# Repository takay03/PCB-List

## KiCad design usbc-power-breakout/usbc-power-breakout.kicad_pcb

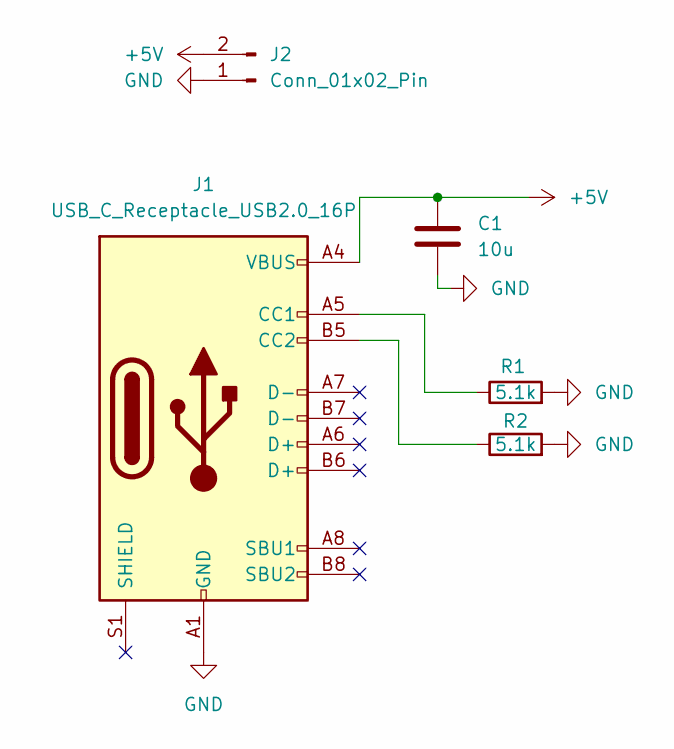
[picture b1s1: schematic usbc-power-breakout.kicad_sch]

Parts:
C1: 10u; C_1206_3216Metric
J1: USB_C_Receptacle_USB2.0_16P; USB_C_Receptacle_GCT_USB4085
J2: Conn_01x02_Pin; PinHeader_1x02_P2.54mm_Vertical
R1, R2: 5.1k; R_1206_3216Metric

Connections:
+5V: C1.1, J1.A4 (VBUS), J1.A9 (VBUS), J1.B4 (VBUS), J1.B9 (VBUS), J2.2
GND: C1.2, J1.A1 (GND), J1.A12 (GND), J1.B1 (GND), J1.B12 (GND), J2.1, R1.2, R2.2
unnamed: J1.A5 (CC1), R1.1
unnamed: J1.B5 (CC2), R2.1

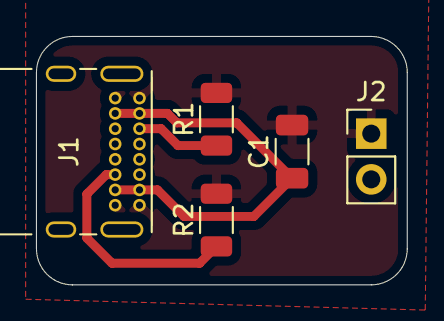
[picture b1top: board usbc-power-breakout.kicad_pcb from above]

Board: 2 copper layers, 20.6 x 13.8 mm, 5 parts (0 on the bottom side), 4 nets.

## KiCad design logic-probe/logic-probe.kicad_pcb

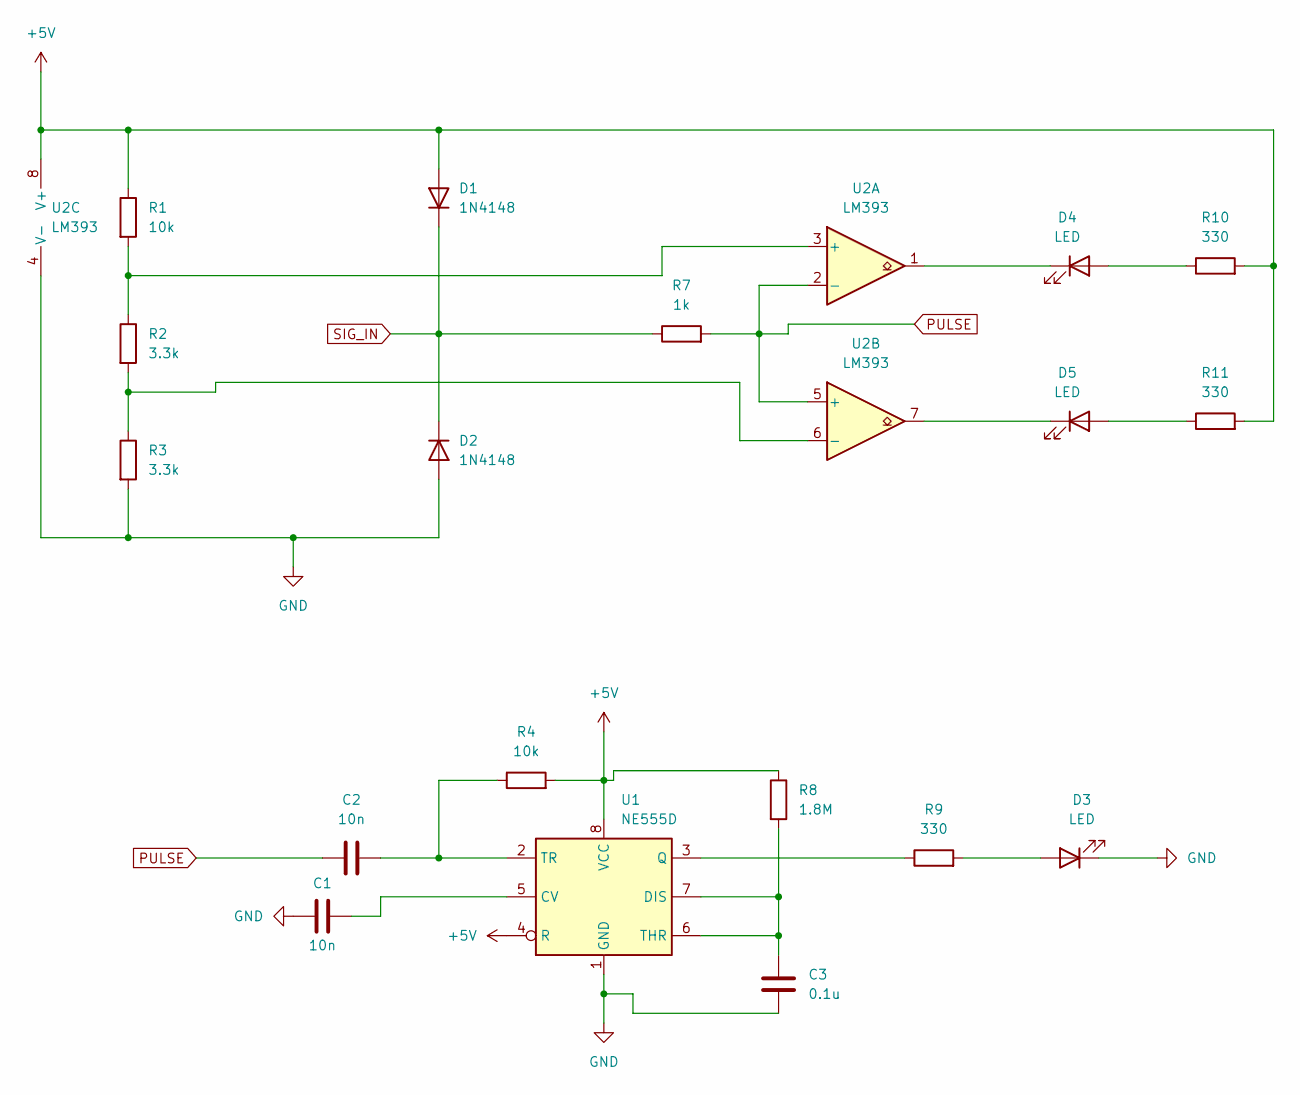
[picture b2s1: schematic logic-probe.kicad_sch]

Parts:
C1, C2: 10n; C_1206_3216Metric
C3: 0.1u; C_1206_3216Metric
D1, D2: 1N4148; D_SOD-123
D3, D4, D5: LED; LED_1206_3216Metric
R1, R4: 10k; R_1206_3216Metric
R2, R3: 3.3k; R_1206_3216Metric
R7: 1k; R_1206_3216Metric
R8: 1.8M; R_0805_2012Metric
R9, R10, R11: 330; R_1206_3216Metric
U1: NE555D; SOIC-8_3.9x4.9mm_P1.27mm
U2: LM393; SOIC-8_3.9x4.9mm_P1.27mm

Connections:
+5V: D1.2 (A), R1.1, R4.2, R8.1, R10.2, R11.2, U1.4 (R), U1.8 (VCC), U2.8 (V+)
GND: C1.1, C3.1, D2.2 (A), D3.1 (K), R3.2, U1.1 (GND), U2.4 (V-)
unnamed: D3.2 (A), R9.2
unnamed: D4.2 (A), R10.1
unnamed: D4.1 (K), U2.1
unnamed: D5.2 (A), R11.1
unnamed: D5.1 (K), U2.7
unnamed: C1.2, U1.5 (CV)
unnamed: C3.2, R8.2, U1.6 (THR), U1.7 (DIS)
unnamed: R9.1, U1.3 (Q)
unnamed: C2.2, R4.1, U1.2 (TR)
unnamed: R1.2, R2.1, U2.3 (+)
unnamed: R2.2, R3.1, U2.6 (-)
PULSE: C2.1, R7.2, U2.2 (-), U2.5 (+)
SIG_IN: D1.1 (K), D2.1 (K), R7.1

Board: 2 copper layers, 19 parts (0 on the bottom side), 15 nets, no tracks yet.

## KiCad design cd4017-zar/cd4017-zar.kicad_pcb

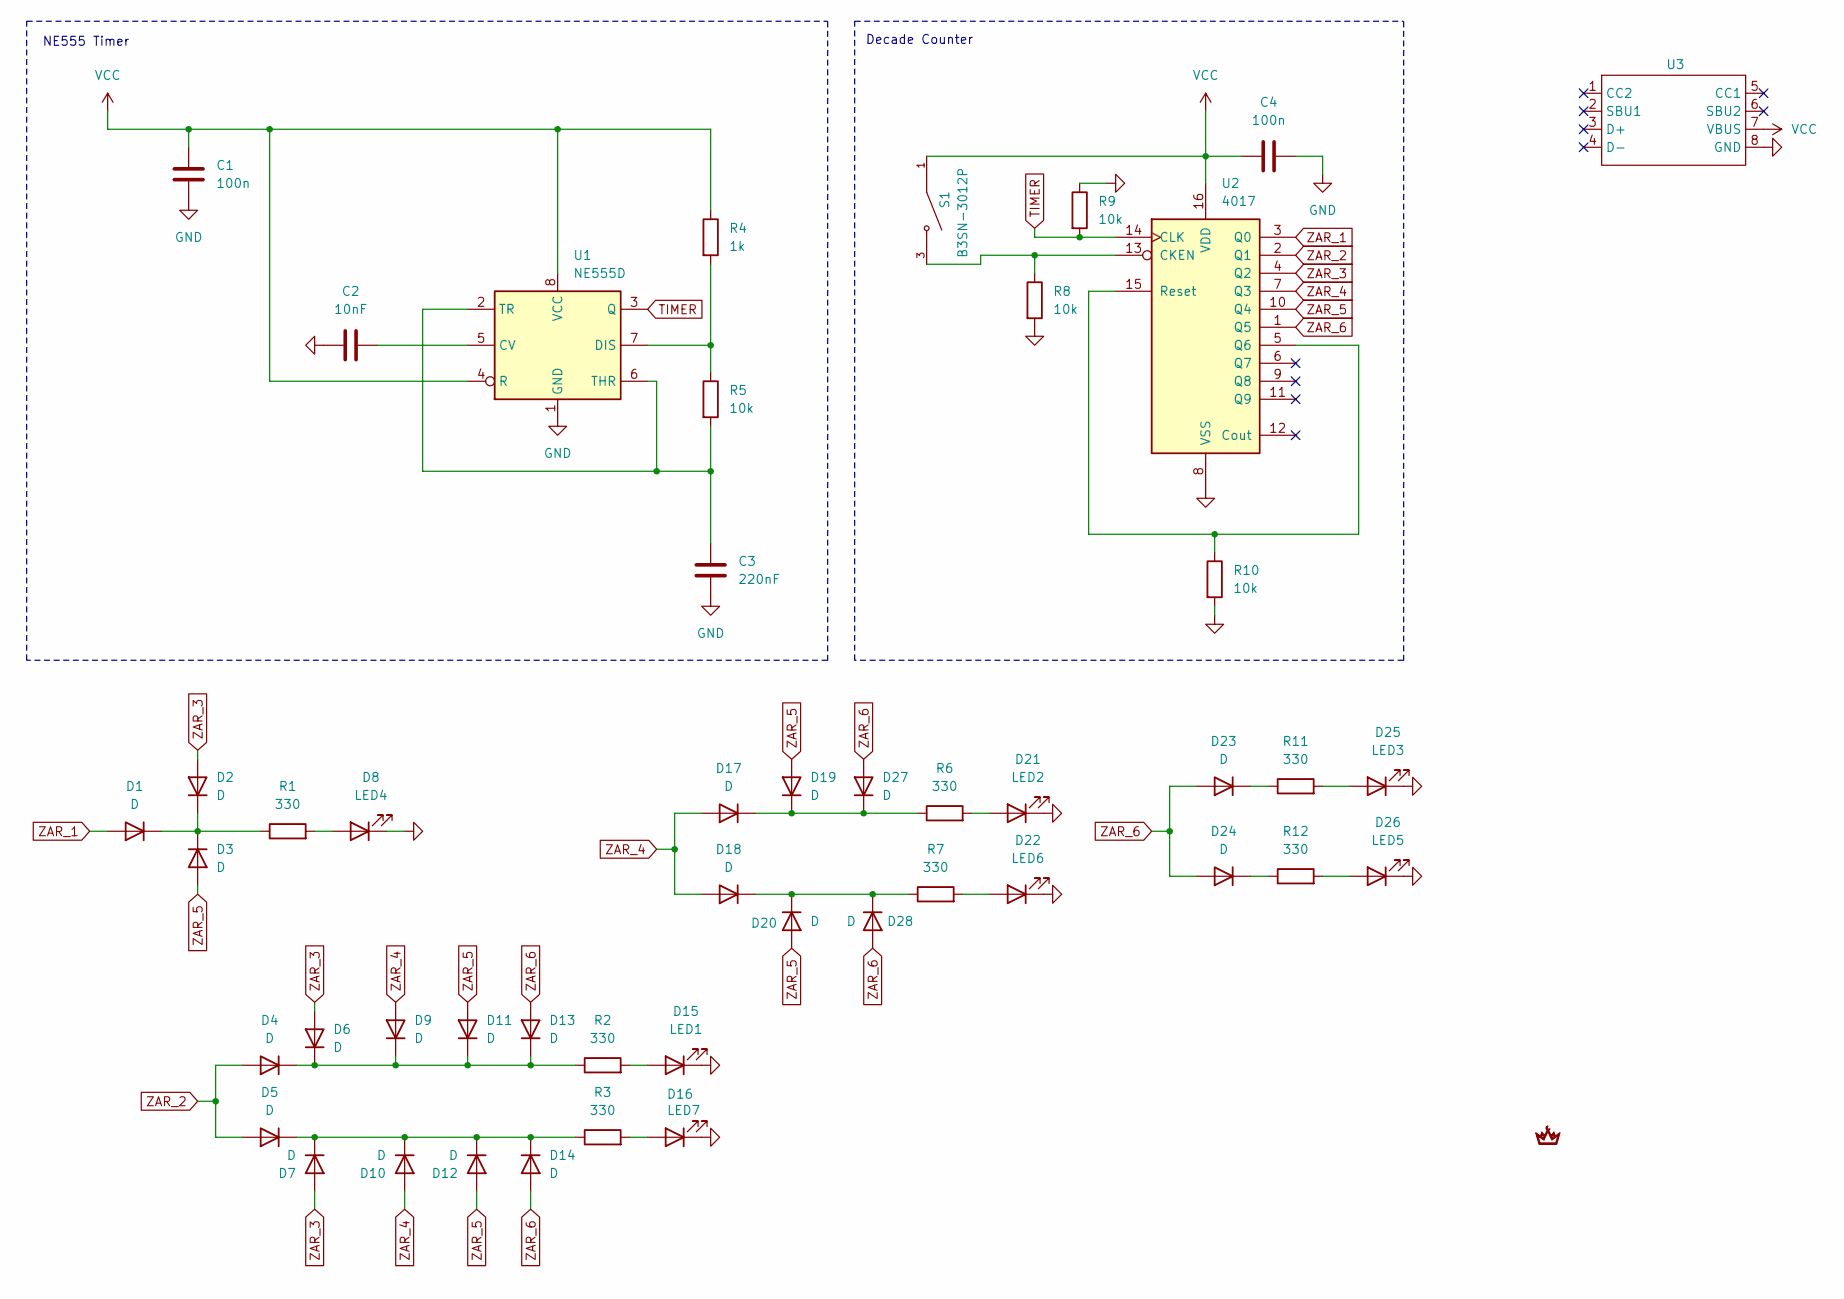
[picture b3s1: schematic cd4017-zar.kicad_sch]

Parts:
C1, C4: 100n; C_1206_3216Metric
C2: 10nF; C_1206_3216Metric
C3: 220nF; C_1206_3216Metric
D1, D2, D3, D4, D5, D6, D7, D9, D10, D11, D12, D13, D14, D17, D18, D19, D20, D23, D24, D27, D28: D; D_SOD-123
D8: LED4; LED_1206_3216Metric
D15: LED1; LED_1206_3216Metric
D16: LED7; LED_1206_3216Metric
D21: LED2; LED_1206_3216Metric
D22: LED6; LED_1206_3216Metric
D25: LED3; LED_1206_3216Metric
D26: LED5; LED_1206_3216Metric
R1, R2, R3, R6, R7, R11, R12: 330; R_1206_3216Metric
R4: 1k; R_1206_3216Metric
R5, R8, R9, R10: 10k; R_1206_3216Metric
S1: B3SN-3012P; SW_B3SN-3012P; PARTREV 0719(0207)(O)
U1: NE555D; SOIC-8_3.9x4.9mm_P1.27mm
U2: 4017; DIP-16_W7.62mm
U3: 4090

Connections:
GND: C1.2, C2.1, C3.2, C4.2, D8.1 (K), D15.1 (K), D16.1 (K), D21.1 (K), D22.1 (K), D25.1 (K), D26.1 (K), R8.2, R9.1, R10.2, U1.1 (GND), U2.8 (VSS), U3.8 (GND)
unnamed: D1.1 (K), D2.1 (K), D3.1 (K), R1.1
unnamed: D8.2 (A), R1.2
unnamed: D5.1 (K), D7.1 (K), D10.1 (K), D12.1 (K), D14.1 (K), R3.1
unnamed: D4.1 (K), D6.1 (K), D9.1 (K), D11.1 (K), D13.1 (K), R2.1
unnamed: D15.2 (A), R2.2
unnamed: D16.2 (A), R3.2
unnamed: D17.1 (K), D19.1 (K), D27.1 (K), R6.1
unnamed: D18.1 (K), D20.1 (K), D28.1 (K), R7.1
unnamed: D21.2 (A), R6.2
unnamed: D22.2 (A), R7.2
unnamed: D23.1 (K), R11.1
unnamed: D24.1 (K), R12.1
unnamed: D25.2 (A), R11.2
unnamed: D26.2 (A), R12.2
unnamed: C2.2, U1.5 (CV)
unnamed: R4.2, R5.1, U1.7 (DIS)
unnamed: C3.1, R5.2, U1.2 (TR), U1.6 (THR)
unnamed: R8.1, S1.3, S1.4, U2.13 (CKEN)
unnamed: R10.1, U2.5 (Q6), U2.15 (Reset)
TIMER: R9.2, U1.3 (Q), U2.14 (CLK)
VCC: C1.1, C4.1, R4.1, S1.1, S1.2, U1.4 (R), U1.8 (VCC), U2.16 (VDD), U3.7 (VBUS)
ZAR_1: D1.2 (A), U2.3 (Q0)
ZAR_2: D4.2 (A), D5.2 (A), U2.2 (Q1)
ZAR_3: D2.2 (A), D6.2 (A), D7.2 (A), U2.4 (Q2)
ZAR_4: D9.2 (A), D10.2 (A), D17.2 (A), D18.2 (A), U2.7 (Q3)
ZAR_5: D3.2 (A), D11.2 (A), D12.2 (A), D19.2 (A), D20.2 (A), U2.10 (Q4)
ZAR_6: D13.2 (A), D14.2 (A), D23.2 (A), D24.2 (A), D27.2 (A), D28.2 (A), U2.1 (Q5)

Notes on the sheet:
Decade Counter
NE555 Timer

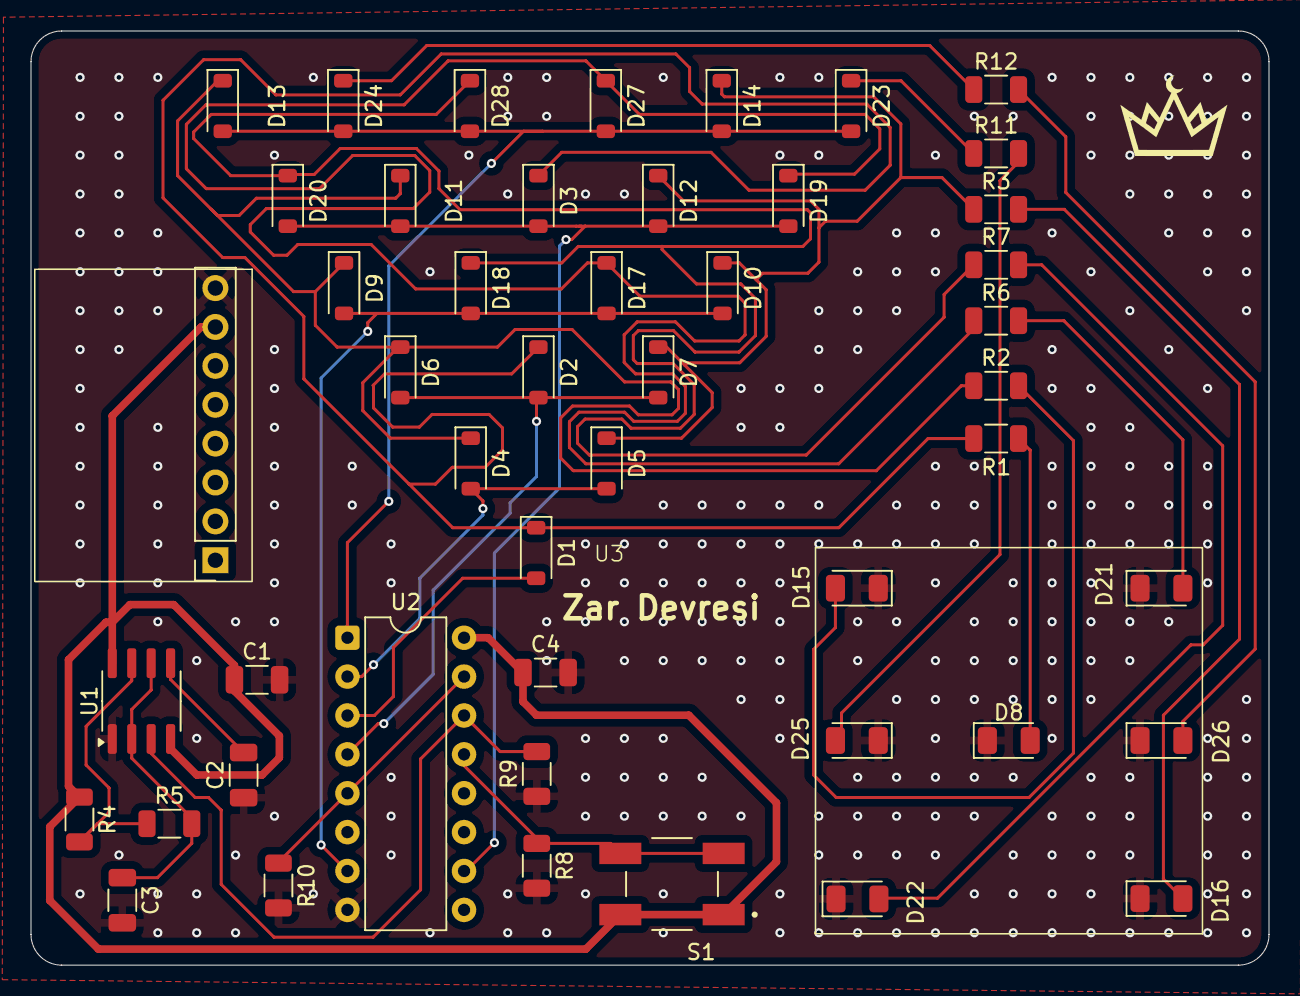
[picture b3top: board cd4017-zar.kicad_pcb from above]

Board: 2 copper layers, 80.9 x 61.0 mm, 48 parts (0 on the bottom side), 28 nets.

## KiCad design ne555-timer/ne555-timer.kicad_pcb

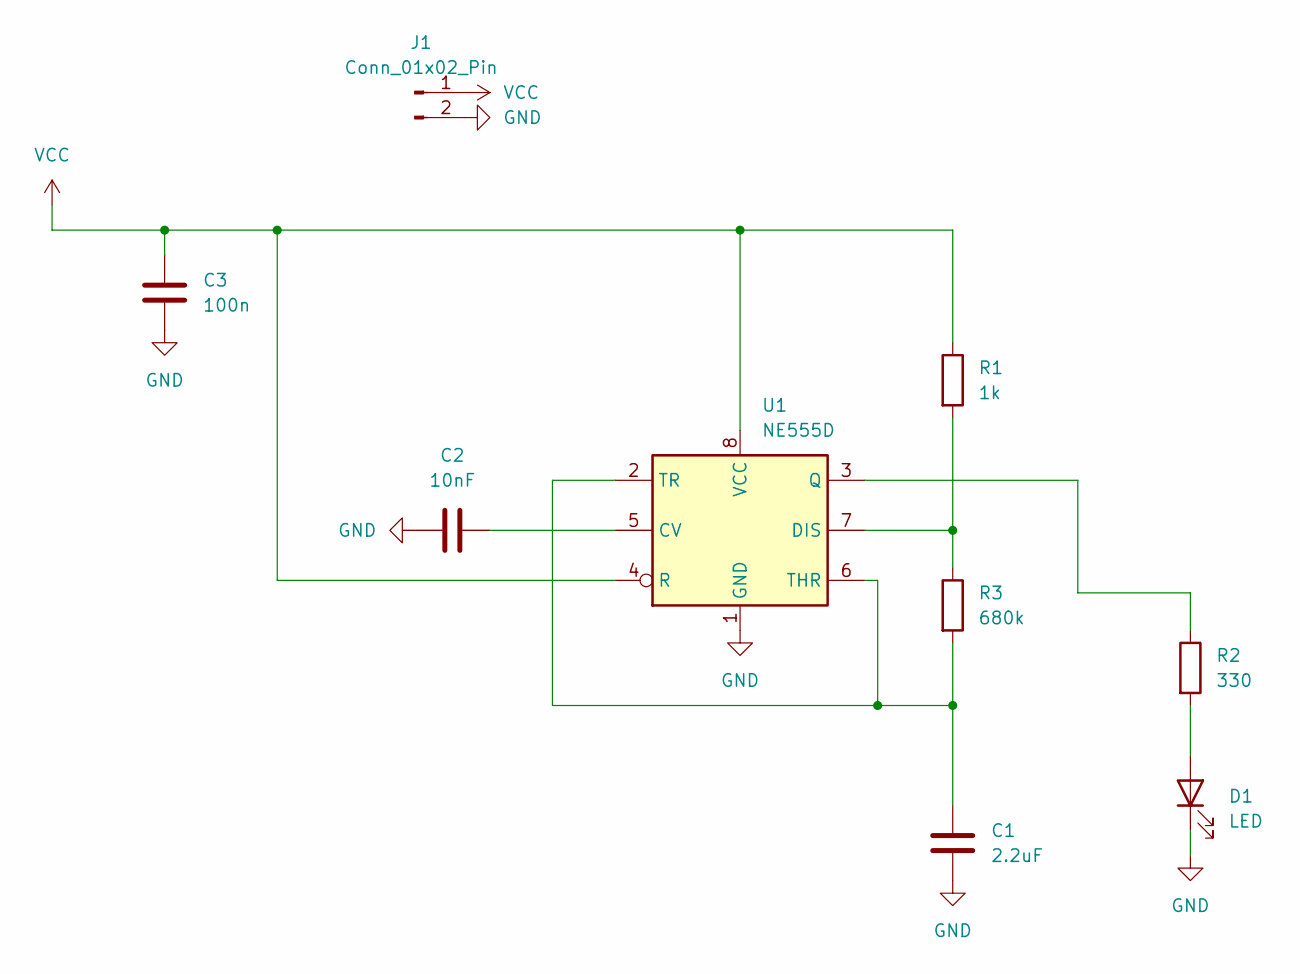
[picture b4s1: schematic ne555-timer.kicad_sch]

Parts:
C1: 2.2uF; C_1206_3216Metric
C2: 10nF; C_1206_3216Metric
C3: 100n; C_1206_3216Metric
D1: LED; LED_1206_3216Metric
J1: Conn_01x02_Pin; PinHeader_1x02_P2.54mm_Vertical
R1: 1k; R_1206_3216Metric
R2: 330; R_1206_3216Metric
R3: 680k; R_1206_3216Metric
U1: NE555D; SOIC-8_3.9x4.9mm_P1.27mm

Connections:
GND: C1.2, C2.1, C3.2, D1.1 (K), J1.2, U1.1 (GND)
unnamed: D1.2 (A), R2.2
unnamed: C2.2, U1.5 (CV)
unnamed: R1.2, R3.1, U1.7 (DIS)
unnamed: R2.1, U1.3 (Q)
unnamed: C1.1, R3.2, U1.2 (TR), U1.6 (THR)
VCC: C3.1, J1.1, R1.1, U1.4 (R), U1.8 (VCC)

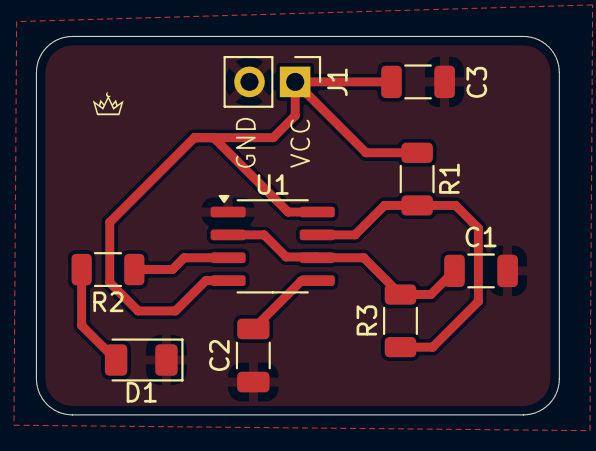
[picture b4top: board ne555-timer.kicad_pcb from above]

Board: 2 copper layers, 29.0 x 21.0 mm, 9 parts (0 on the bottom side), 7 nets.

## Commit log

2026-05-16 timer devresi eklendi
2026-05-16 pcb listesi eklendi
2026-05-18 zar devresi şematiği eklendi ve pcb listesi yenilendi
2026-05-22 zar footprint i eklendi
2026-05-24 logic-probe şematiği eklendi
2026-05-24 pcb listesinin ismi değiştirildi
2026-05-24 yeni indexe eski verilerin yüklenmesi için seçenek eklendi
2026-05-25 usb c power board unun şematiği yapıldı - footprint yapıldı ama erc hataları düzeltilecek
